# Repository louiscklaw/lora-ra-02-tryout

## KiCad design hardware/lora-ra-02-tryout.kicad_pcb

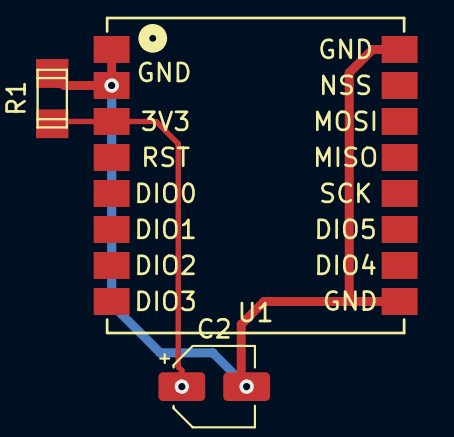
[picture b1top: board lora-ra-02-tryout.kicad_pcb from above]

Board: 2 copper layers, 4 parts (1 on the bottom side), 2 nets.

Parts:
C1: C104,0603; C_0603_1608Metric_Pad1.05x0.95mm_HandSolder
C2: CP22uf,16V; CP_Elec_4x5.3
R1: VAR_3V3,1206; VAR_1206
U1: Ai-Thinker-Ra-02; Ai-Thinker-Ra-02-LoRa

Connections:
+3V3: C1.1, C2.1, R1.2, U1.3
GND: C1.2, C2.2, R1.1, U1.1, U1.2, U1.9, U1.16

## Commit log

2019-06-11 update,
2019-06-11 update for creating project,
2020-05-05 ci: init travis build config,
2020-05-05 ci: init travis token,
